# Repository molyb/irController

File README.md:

# irController

[PCB board](pcb) and [firmware](firmware)

# Mode Select
## Normal Mode
This mode can control consumer electronics.  

1. Just turn on or release the reset button.
2. Access the ip address that allocated by your router. 

## Network Config Mode
This mode configure Wi-Fi.
   
1. Press program button within one second of releasing the reset button,
    and hold down it for one second.
2. Connect to IR_CONTROLLER_AP.
3. You will be redirected to the configuration page automatically.
4. Input ssid and password, and click save button.

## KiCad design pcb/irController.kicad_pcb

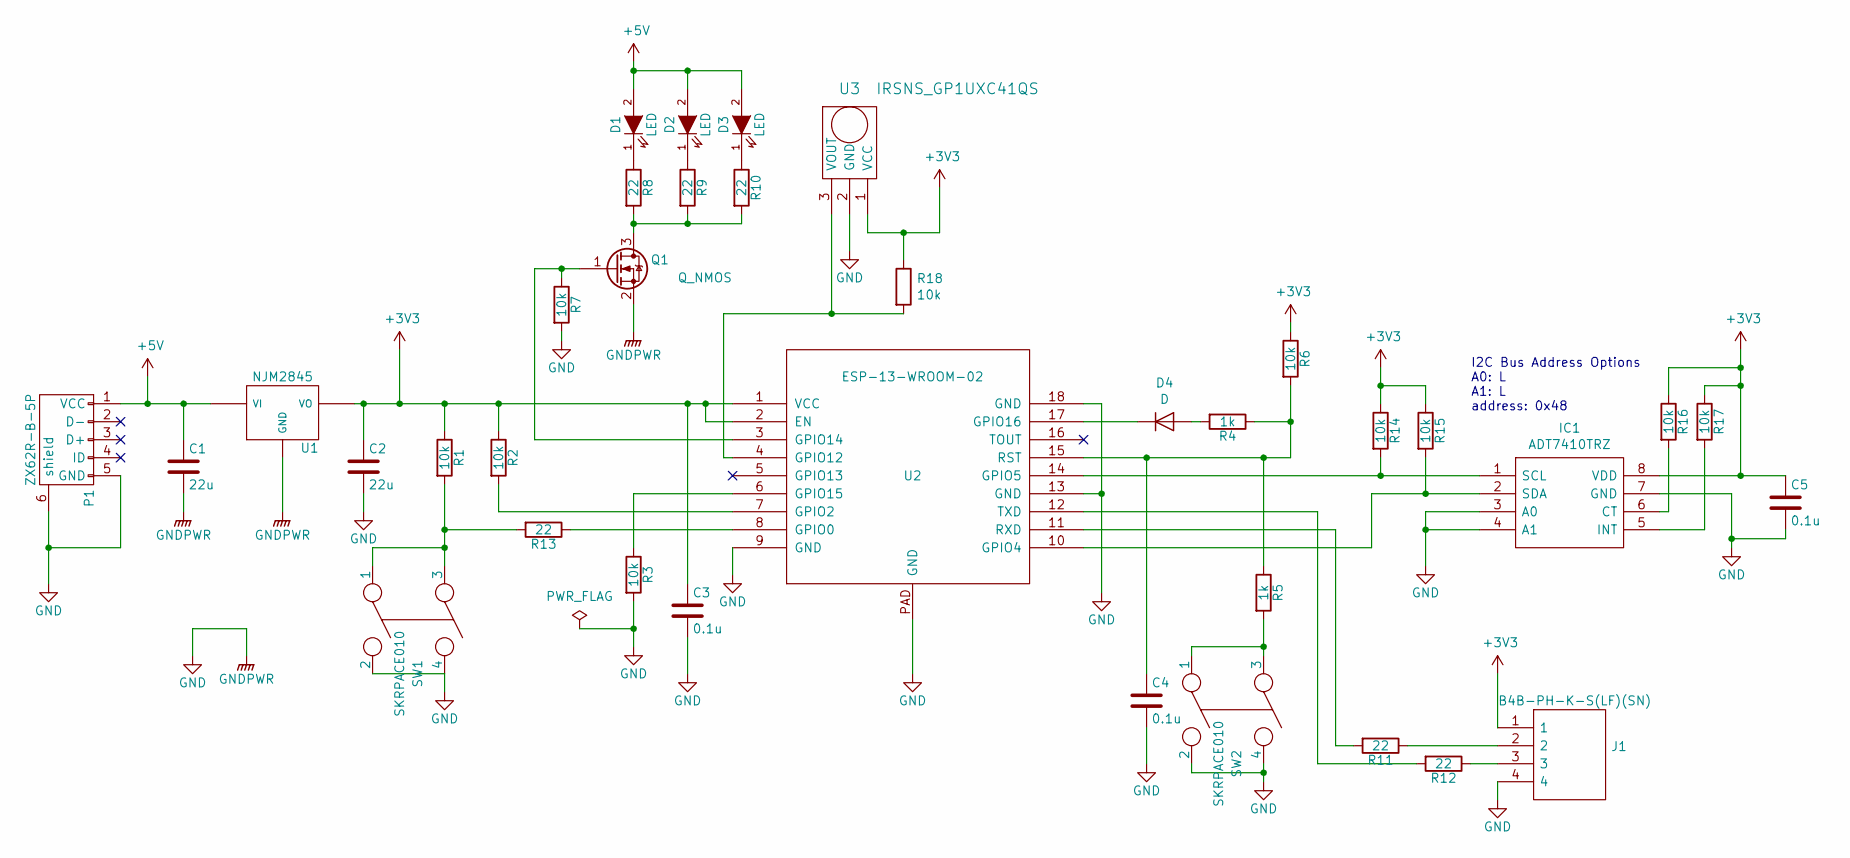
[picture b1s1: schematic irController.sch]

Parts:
C1, C2: 22u; C_1206_3216Metric
C3, C4, C5: 0.1u; C_0603_1608Metric
D1, D2, D3: LED; LED-5MM
D4: D; D_SOD-123F
IC1: ADT7410TRZ; SOIC127P600X175-8N; Manufacturer_Part_Number ADT7410TRZ; Mouser Part Number 584-ADT7410TRZ
J1: B4B-PH-K-S(LF)(SN); SHDR4W60P0X200_1X4_990X450X600P; Manufacturer_Part_Number B4B-PH-K-S(LF)(SN)
P1: ZX62R-B-5P; USB_Micro-B_Wuerth_629105150521
Q1: Q_NMOS; SOT-23
R1, R2, R3, R6, R7, R14, R15, R16, R17, R18: 10k; R_0603_1608Metric
R4, R5: 1k; R_0603_1608Metric
R8, R9, R10, R11, R12, R13: 22; R_0603_1608Metric
SW1, SW2: SKRPACE010
U1: NJM2845; TO-252-3
U2: ESP-13-WROOM-02
U3: IRSNS_GP1UXC41QS; Socket_Strip_Straight_1x03

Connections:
+3V3: C2.1, C3.1, C5.1, IC1.8 (VDD), J1.1, R1.1, R2.1, R6.1, R14.1, R15.1, R16.1, R17.1, R18.1, U1.VO, U2.1 (VCC), U2.2 (EN), U3.1 (VCC); also elsewhere on the board
+5V: C1.1, D1.2 (A), D2.2 (A), D3.2 (A), P1.1 (VCC), U1.VI
GND: C1.2, C2.2, C3.2, C4.2, C5.2, IC1.3 (A0), IC1.4 (A1), IC1.7 (GND), J1.4, P1.5 (GND), P1.6 (shield), Q1.2 (S), R3.2, R7.2, SW1.2, SW1.4, SW2.2, SW2.4, U1.GND, U2.9 (GND), U2.13 (GND), U2.18 (GND), U2.PAD (GND), U3.2 (GND); also elsewhere on the board
unnamed: C4.1, R4.1, R5.1, R6.2, U2.15 (RST)
unnamed: D1.1 (K), R8.1
unnamed: D2.1 (K), R9.1
unnamed: D3.1 (K), R10.1
unnamed: D4.1 (K), U2.17 (GPIO16)
unnamed: D4.2 (A), R4.2
unnamed: IC1.1 (SCL), R14.2, U2.14 (GPIO5)
unnamed: IC1.2 (SDA), R15.2, U2.10 (GPIO4)
unnamed: IC1.5 (INT), R17.2
unnamed: IC1.6 (CT), R16.2
unnamed: J1.2, R11.1
unnamed: J1.3, R12.1
unnamed: Q1.1 (G), R7.1, U2.3 (GPIO14)
unnamed: Q1.3 (D), R8.2, R9.2, R10.2
unnamed: R1.2, R13.2, SW1.1, SW1.3
unnamed: R2.2, U2.7 (GPIO2)
unnamed: R3.1, U2.6 (GPIO15)
unnamed: R5.2, SW2.1, SW2.3
unnamed: R11.2, U2.11 (RXD)
unnamed: R12.2, U2.12 (TXD)
unnamed: R13.1, U2.8 (GPIO0)
unnamed: R18.2, U2.4 (GPIO12), U3.3 (VOUT)
unnamed 25: U2.5 (GPIO13); also elsewhere on the board

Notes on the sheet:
I2C Bus Address Options A0: L A1: L address: 0x48

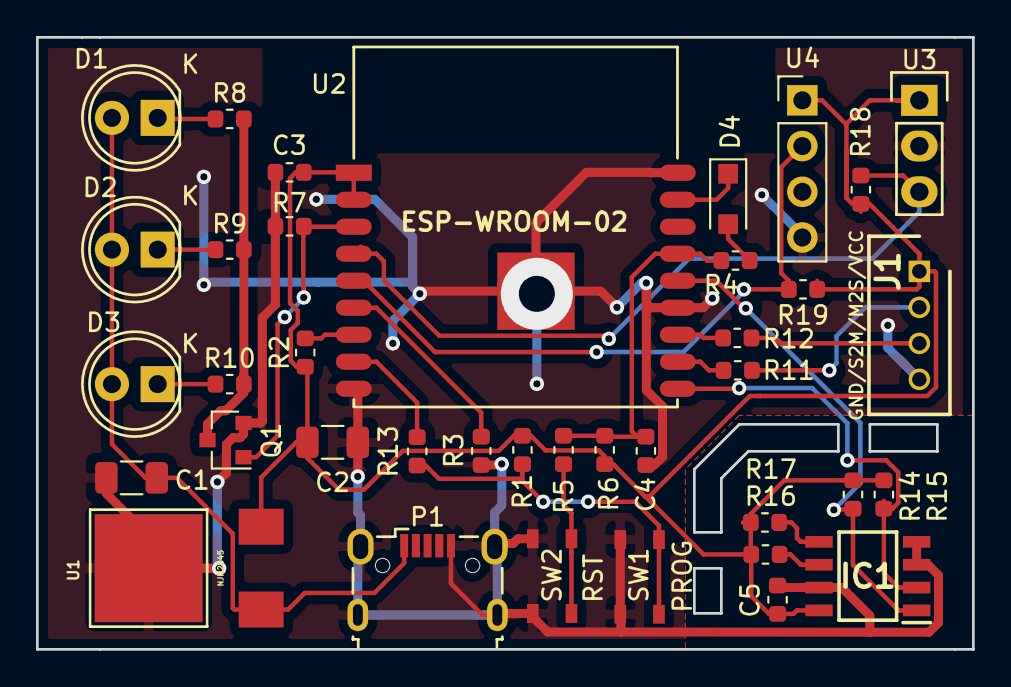
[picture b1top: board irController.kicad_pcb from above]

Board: 2 copper layers, 52.0 x 34.0 mm, 38 parts (0 on the bottom side), 26 nets.

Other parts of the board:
R19: 10k; R_0603_1608Metric
U4: DHT11; PinHeader_1x04_P2.54mm_Vertical

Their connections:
+3V3: R19.1, U4.1; also elsewhere on the board
GND: U4.4; also elsewhere on the board
unnamed 25: R19.2, U4.2; also elsewhere on the board

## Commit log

2020-01-05 1st commit
2020-01-05 バックアップファイル等削除し整理
2020-01-05 コネクタ変更
2020-01-05 一旦完成
2020-03-28 発注時データ
2020-03-28 フォルダ移動
2020-03-29 gitignoreファイルを追加
2020-03-29 ユーザ用ボタンをリセットボタンに変更
2020-03-29 git管理不要なファイルを管理対象から削除
2020-03-29 通信線の誤配線を修正
2020-03-29 温度センサ搭載
2020-03-29 ライブラリをサブモジュールとしてプロジェクト内に持たせた
2020-03-29 DRC対応
2020-03-29 LEDの電源電圧を選択できるようにした
2020-03-29 パターン引いた
2020-03-31 LEDの駆動電流は5V固定にした
2020-03-31 発注データ
2020-03-31 回路とファームを一元管理
2020-04-26 IC発熱を考慮して再配置
2020-05-30 プロジェクト設定
    依存ライブラリ設定等
    フォルダ名を変えたら自動でプロジェクト名も変わった
    (cherry picked from commit d78a6416cff3c20f1487afc298246e52a0f54fb1)
2020-05-30 実運用できる形に修正
2020-05-30 アップロード処理を追加した
2020-05-30 所定の時刻に任意の処理をコールする機能を追加
    platformio.iniでプラットフォームバージョンを指定しているのは
    最新バージョンのconfigTime関数にバグがあるため
2020-05-30 エアコン自動制御が入った際に任意の処理を挿入できるようにした
2020-06-14 WebUI上からエアコンを制御できるようにした
2020-06-14 WebUIから照明制御できるようにした
2020-06-14 トップページに各ページへのリンクを貼った
2020-06-14 callbackが正常に呼び出せない問題を修正
2020-06-27 Webサーバ用のデータをファイルシステム上のhtmlファイルに格納するようにした
2020-07-04 lightのハンドラもhtml化
2020-07-11 JSでHTMLパラメータを変更
2020-07-11 イベントをEEPROMに格納するクラスを作成
2020-07-11 bug fix
2020-07-11 EEPROMの値に基づきイベントを登録するようにした
2020-07-11 EEPROMに登録した情報をJSONで返すようにした
2020-07-11 チェックボックス表示
2020-07-24 イベント削除処理追加
2020-07-24 eepromからイベントerase時にチェックサムが不正値になってしまっていた問題を修正
2020-07-24 イベントがdeleteできない不具合を修正
2020-07-24 tickerの設定が更新できていなかった問題を修正
2020-07-24 冗長なシリアル出力を削除
2020-07-24 index.htmlからイベント設定ページに飛べるようにした
2020-07-25 webページ上でイベントが実行される曜日を設定および表示ができるようにした
    実際の発火処理はまだ
2020-07-25 POSTとGETで関数分割
2020-07-25 イベント実行週の設定が無い場合は登録しないように修正
2020-07-25 JSON用のメモリサイズ変更と最低限の保護処理追加
2020-07-26 曜日対応ひとまず書ききった
    未検証
2020-07-26 bugfix
2020-07-26 トップページリンク追加とリファクタリング
2020-07-26 ambientへのデータ登録処理有効化
2020-07-26 不要なコメント削除
2020-07-26 add LICENSE
2020-08-13 separate control and drawing for AC
2020-08-13 fix spelling of the header
2020-08-13 add function to display last state
2020-08-14 post control parameters by ajax
2020-08-14 change position of script tags
2020-08-14 reference local file of jquery
2020-08-29 Split functions by each mode
2020-08-29 fix http post
2020-08-29 add page for config ssid
2020-08-29 add form for network config
2020-08-29 add load function of ssid and pw
2020-08-30 optimize usage memory
2020-08-30 write readme about mode select
2020-12-05 correspond to heating start of AC
2020-12-05 Create LICENSE
    add a license file

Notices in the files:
pcb/irController.kicad_pcb:
(C) 2020 MolybYngFl
